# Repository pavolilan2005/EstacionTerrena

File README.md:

# EstacionTerrena
Esta estación terrena es un sistema compacto, portátil e independiente diseñado para la recepción, procesamiento y visualización en tiempo real de datos telemétricos provenientes de un nodo remoto. El sistema se comunica por radiofrecuencia y cuenta con una interfaz local y web integrada.

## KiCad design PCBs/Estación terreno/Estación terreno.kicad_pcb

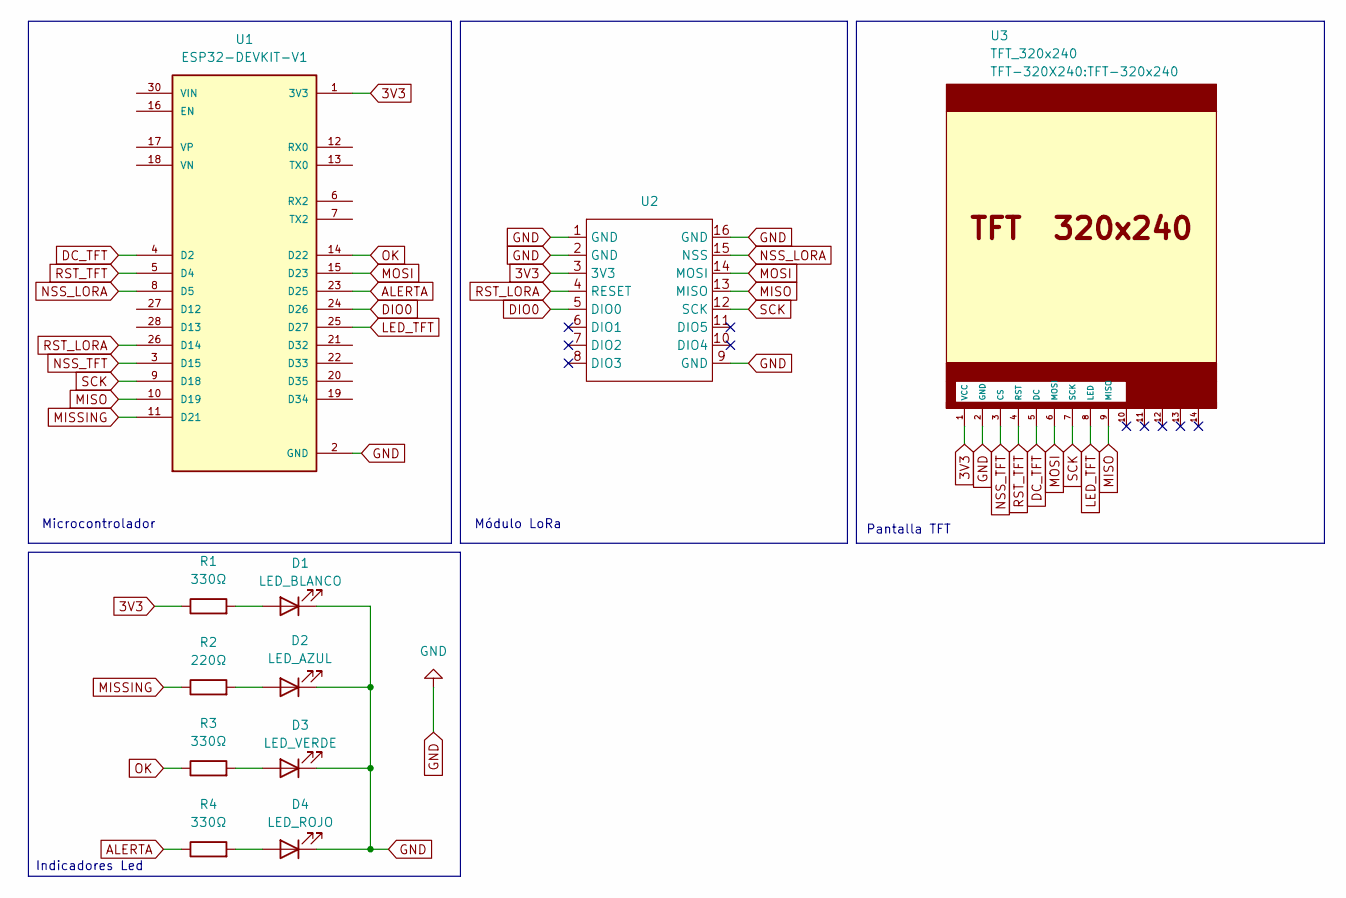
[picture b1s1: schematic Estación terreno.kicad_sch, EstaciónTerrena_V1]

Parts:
D1: LED_BLANCO; LED_D5.0mm
D2: LED_AZUL; LED_D5.0mm
D3: LED_VERDE; LED_D5.0mm
D4: LED_ROJO; LED_D5.0mm
R1, R3, R4: 330Ω; R_Axial_DIN0207_L6.3mm_D2.5mm_P15.24mm_Horizontal
R2: 220Ω; R_Axial_DIN0207_L6.3mm_D2.5mm_P15.24mm_Horizontal
U1: ESP32-DEVKIT-V1; MODULE_ESP32_DEVKIT_V1; PARTREV N/A
U2: LoraSX1278
U3: TFT_320x240; TFT-320x240

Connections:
3V3: R1.1, U1.1 (3V3), U2.3 (3V3), U3.1 (VCC)
ALERTA: R4.1, U1.23 (D25)
DC_TFT: U1.4 (D2), U3.5 (DC)
DIO0: U1.24 (D26), U2.5 (DIO0)
GND: D1.1 (K), D2.1 (K), D3.1 (K), D4.1 (K), U1.2 (GND), U1.29 (GND), U2.1 (GND), U2.2 (GND), U2.9 (GND), U2.16 (GND), U3.2 (GND)
LED_TFT: U1.25 (D27), U3.8 (LED)
MISO: U1.10 (D19), U2.13 (MISO), U3.9 (MISO)
MISSING: R2.1, U1.11 (D21)
MOSI: U1.15 (D23), U2.14 (MOSI), U3.6 (MOSI)
NSS_LORA: U1.8 (D5), U2.15 (NSS)
NSS_TFT: U1.3 (D15), U3.3 (CS)
unnamed: D1.2 (A), R1.2
unnamed: D2.2 (A), R2.2
unnamed: D3.2 (A), R3.2
unnamed: D4.2 (A), R4.2
OK: R3.1, U1.14 (D22)
RST_LORA: U1.26 (D14), U2.4 (RESET)
RST_TFT: U1.5 (D4), U3.4 (RST)
SCK: U1.9 (D18), U2.12 (SCK), U3.7 (SCK)

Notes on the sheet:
Módulo LoRa
Pantalla TFT
Indicadores Led
Microcontrolador

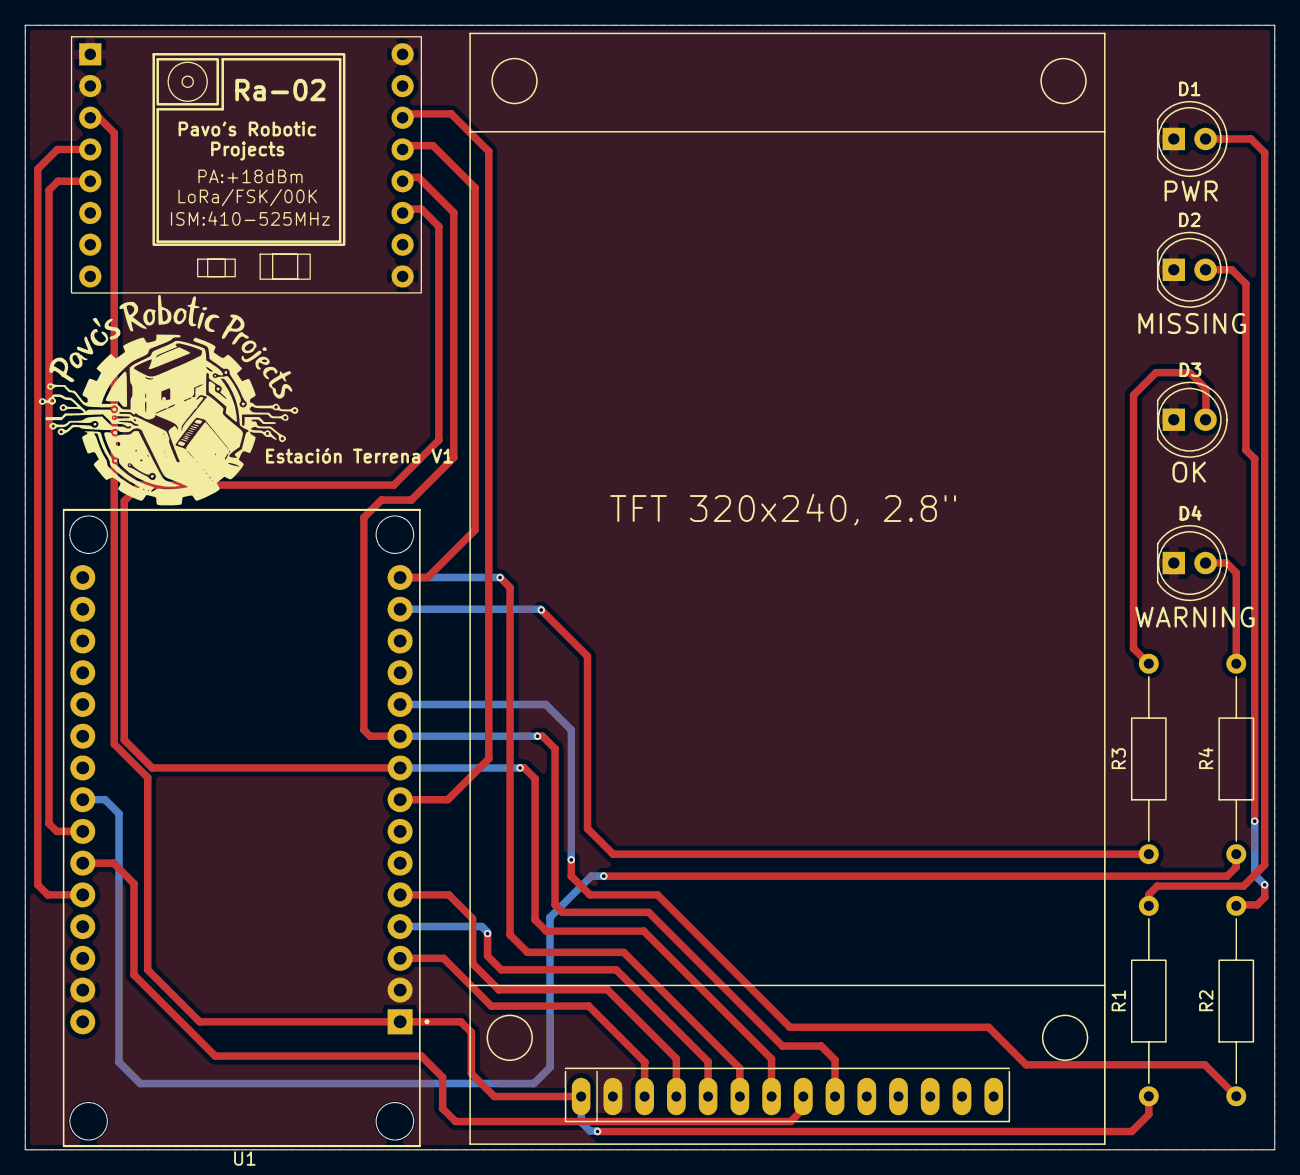
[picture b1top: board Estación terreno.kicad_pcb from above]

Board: 2 copper layers, 100.0 x 90.0 mm, 11 parts (0 on the bottom side), 19 nets.
